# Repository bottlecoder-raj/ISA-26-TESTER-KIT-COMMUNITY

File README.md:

# ISA-26-TESTER-KIT-COMMUNITY
[Check the document](https://docs.google.com/spreadsheets/d/1PZvV7h6_lfP_2LBilbgCukRlQuz8yBCOUH9IjQd16hU/edit?gid=0#gid=0)

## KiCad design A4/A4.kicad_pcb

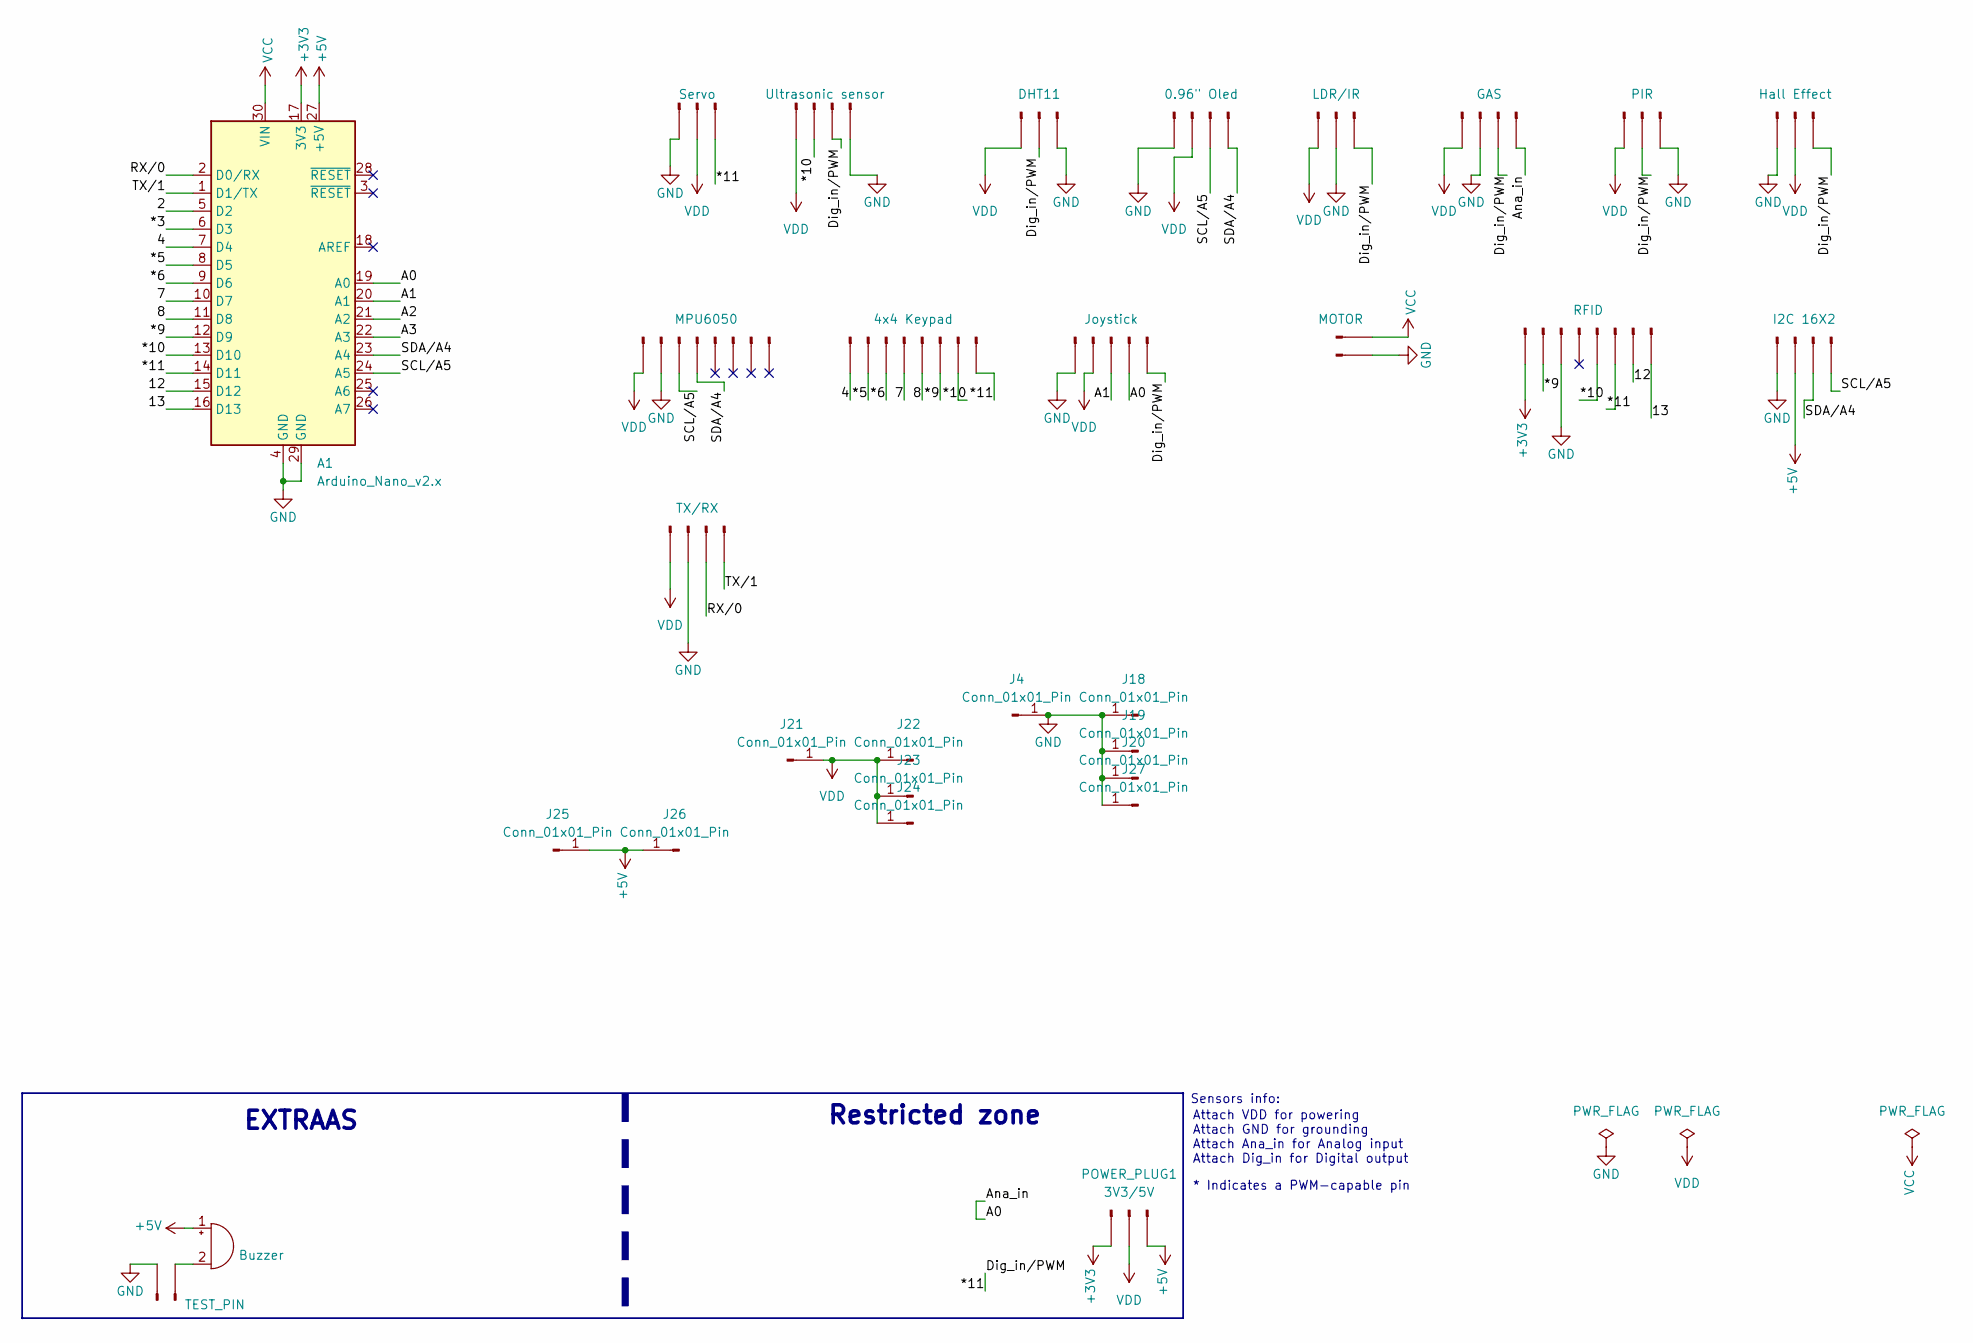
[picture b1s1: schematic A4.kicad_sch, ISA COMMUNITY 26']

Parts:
A1: Arduino_Nano_v2.x; Arduino_Nano
BZ1: Buzzer; TerminalBlock_Phoenix_MKDS-1,5-2-5.08_1x02_P5.08mm_Horizont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
J1: RFID; PinHeader_1x08_P2.54mm_Vertical
J2: I2C 16X2; PinHeader_1x04_P2.54mm_Vertical
J3: TX/RX; PinHeader_1x04_P2.54mm_Vertical
J4, J18, J19, J20, J21, J22, J23, J24, J25, J26, J27: Conn_01x01_Pin; PinHeader_1x01_P2.54mm_Vertical
J5: Servo; PinSocket_1x03_P2.54mm_Vertical
J6: Ultrasonic sensor; PinSocket_1x04_P2.54mm_Vertical
J7: DHT11; PinSocket_1x03_P2.54mm_Vertical
J8: TEST_PIN; PinSocket_1x02_P2.54mm_Vertical
J9: 0.96" Oled; PinSocket_1x04_P2.54mm_Vertical
J10: LDR/IR; PinSocket_1x03_P2.54mm_Vertical
J11: GAS; PinSocket_1x04_P2.54mm_Vertical
J12: PIR; PinSocket_1x03_P2.54mm_Vertical
J13: Hall Effect; PinSocket_1x03_P2.54mm_Vertical
J14: MPU6050; PinSocket_1x08_P2.54mm_Vertical
J15: 4x4 Keypad; PinSocket_1x08_P2.54mm_Vertical
J16: Joystick; PinSocket_1x05_P2.54mm_Vertical
J17: MOTOR; TerminalBlock_Phoenix_MKDS-1,5-2-5.08_1x02_P5.08mm_Horizont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
POWER_PLUG1: 3V3/5V; PinSocket_1x03_P2.54mm_Vertical

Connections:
+3V3: A1.17 (3V3), J1.8, POWER_PLUG1.3
+5V: A1.27 (+5V), BZ1.1 (+), J2.3, J25.1 (Pin_1_1), J26.1 (Pin_1_1), POWER_PLUG1.1
/2: A1.5 (D2)
/4: A1.7 (D4), J15.8
/7: A1.10 (D7), J15.5
/8: A1.11 (D8), J15.4
/12: A1.15 (D12), J1.2
/13: A1.16 (D13), J1.1
/*3: A1.6 (D3)
/*5: A1.8 (D5), J15.7
/*6: A1.9 (D6), J15.6
/*9: A1.12 (D9), J1.7, J15.3
/*10: A1.13 (D10), J1.4, J6.3, J15.2
/*11: A1.14 (D11), J1.3, J5.1, J6.2, J7.2, J10.1, J11.2, J12.2, J13.1, J15.1, J16.1
/A0: A1.19 (A0), J11.1, J16.2
/A1: A1.20 (A1), J16.3
/A2: A1.21 (A2)
/A3: A1.22 (A3)
/RX/0: A1.2 (D0/RX), J3.2
/SCL/A5: A1.24 (A5), J2.1, J9.2, J14.6
/SDA/A4: A1.23 (A4), J2.2, J9.1, J14.5
/TX/1: A1.1 (D1/TX), J3.1
GND: A1.4 (GND), A1.29 (GND), J1.6, J2.4, J3.3, J4.1 (Pin_1_1), J5.3, J6.1, J7.1, J8.1, J9.4, J10.2, J11.3, J12.1, J13.3, J14.7, J16.5, J17.2, J18.1 (Pin_1_1), J19.1 (Pin_1_1), J20.1 (Pin_1_1), J27.1 (Pin_1_1)
unnamed: BZ1.2 (-), J8.2
VCC: A1.30 (VIN), J17.1
VDD: J3.4, J5.2, J6.4, J7.3, J9.3, J10.3, J11.4, J12.3, J13.2, J14.8, J16.4, J21.1 (Pin_1_1), J22.1 (Pin_1_1), J23.1 (Pin_1_1), J24.1 (Pin_1_1), POWER_PLUG1.2

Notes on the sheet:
Attach VDD for powering Attach GND for grounding Attach Ana_in for Analog input Attach Dig_in for Digital output
Sensors info:
* Indicates a PWM-capable pin
Restricted zone
EXTRAAS

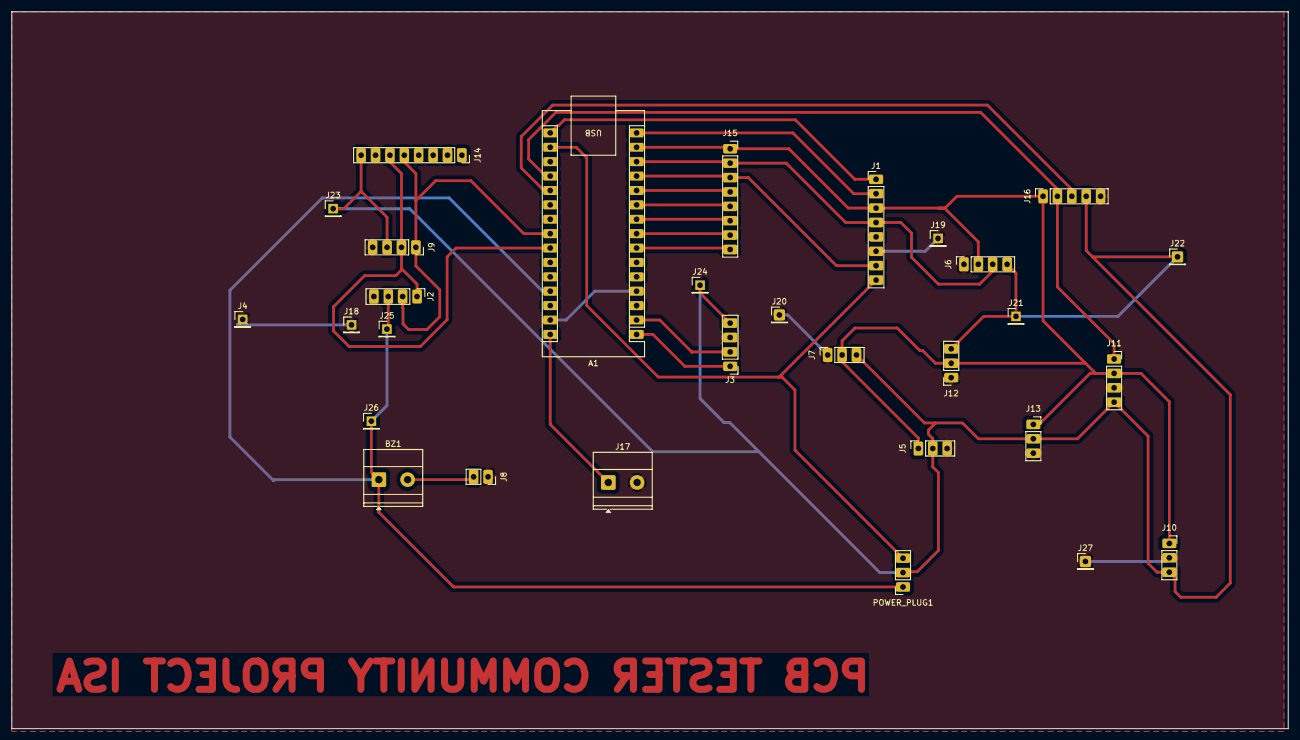
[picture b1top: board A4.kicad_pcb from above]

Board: 2 copper layers, 225.2 x 126.5 mm, 30 parts (0 on the bottom side), 22 nets.
